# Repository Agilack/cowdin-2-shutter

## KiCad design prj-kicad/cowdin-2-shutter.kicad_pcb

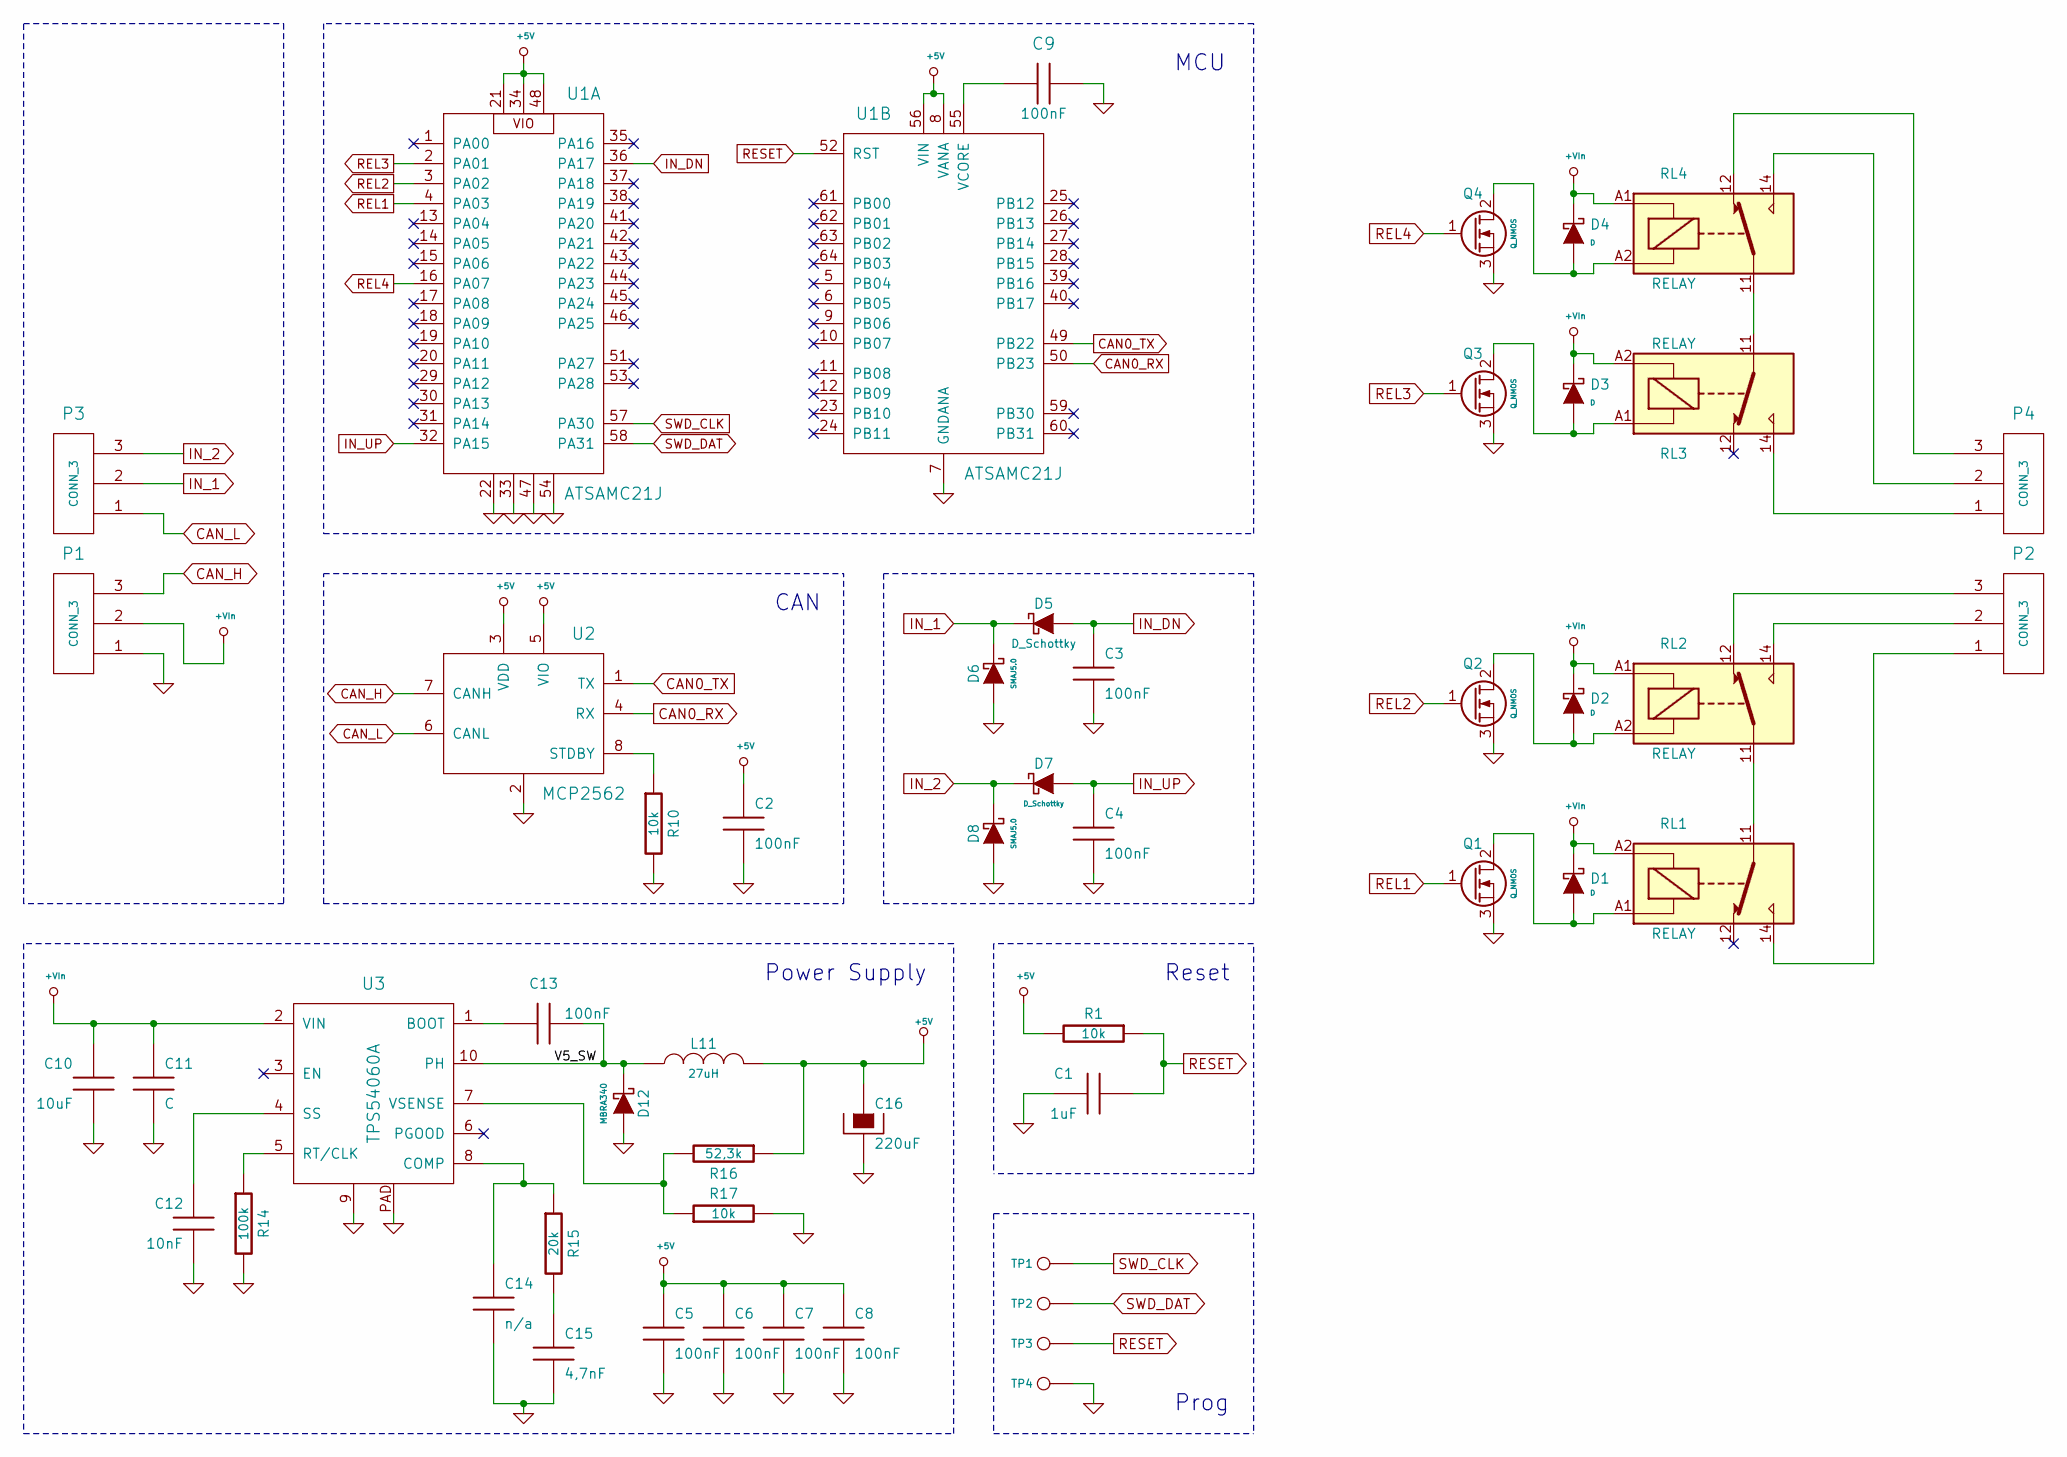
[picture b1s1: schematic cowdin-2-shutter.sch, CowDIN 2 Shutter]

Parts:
C1: 1uF; SMD0603
C2, C3, C4, C5, C6, C7, C8, C9, C13: 100nF; SMD0603
C10: 10uF; SMD1210
C11: C; SMD1210
C12: 10nF; SMD0603
C14: n/a; SMD0603
C15: 4,7nF; SMD0603
C16: 220uF; C_TPB_D4
D1, D2, D3, D4: D; SOD-123
D5, D7: D_Schottky; SOD-123
D6, D8: SMAJ5.0; DO214AC
D12: MBRA340; DO214AC
L11: 27uH; I_MSS1048
P1, P2, P3, P4: CONN_3; CONN_MC000035
Q1, Q2, Q3, Q4: Q_NMOS; SOT23-3
R1, R10, R17: 10k; SMD0603
R14: 100k; SMD0603
R15: 20k; SMD0603
R16: 52,3k; SMD0603
RL1, RL2, RL3, RL4: RELAY; RL_3451
TP1, TP2, TP3, TP4: CONN_1; TP_SMD
U1: ATSAMC21J; TQFP64
U2: MCP2562; SOIC-8E
U3: TPS54060A; MSOP10p

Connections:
5V: C2.1, C5.1, C6.1, C7.1, C8.1, C16.1, L11.2, R1.2, R16.1, U1.8 (VANA), U1.21, U1.34, U1.48, U1.56 (VIN), U2.3 (VDD), U2.5 (VIO)
/V5_SW: C13.2, D12.2 (K), L11.1, U3.10 (PH)
CAN0_RX: U1.50 (PB23), U2.4 (RX)
CAN0_TX: U1.49 (PB22), U2.1 (TX)
CAN_H: P1.3, U2.7 (CANH)
CAN_L: P3.1, U2.6 (CANL)
GND: C1.2, C2.2, C3.2, C4.2, C5.2, C6.2, C7.2, C8.2, C9.1, C10.2, C11.2, C12.2, C14.2, C15.2, C16.2, D6.1 (A), D8.1 (A), D12.1 (A), P1.1, Q1.3 (S), Q2.3 (S), Q3.3 (S), Q4.3 (S), R10.2, R14.2, R17.2, TP4.1, U1.7 (GNDANA), U1.22, U1.33, U1.47, U1.54, U2.2, U3.9, U3.PAD
IN_1: D5.2 (K), D6.2 (K), P3.2
IN_2: D7.2 (K), D8.2 (K), P3.3
IN_DN: C3.1, D5.1 (A), U1.36 (PA17)
IN_UP: C4.1, D7.1 (A), U1.32 (PA15)
unnamed: C9.2, U1.55 (VCORE)
unnamed: C12.1, U3.4 (SS)
unnamed: C13.1, U3.1 (BOOT)
unnamed: C14.1, R15.1, U3.8 (COMP)
unnamed: C15.1, R15.2
unnamed: D1.1 (A), Q1.2 (D), RL1.A1
unnamed: D2.1 (A), Q2.2 (D), RL2.A2
unnamed: D3.1 (A), Q3.2 (D), RL3.A1
unnamed: D4.1 (A), Q4.2 (D), RL4.A2
unnamed: P2.1, RL1.14
unnamed: P2.2, RL2.14
unnamed: P2.3, RL2.12
unnamed: P4.1, RL3.14
unnamed: P4.2, RL4.14
unnamed: P4.3, RL4.12
unnamed: R10.1, U2.8 (STDBY)
unnamed: R14.1, U3.5 (RT/CLK)
unnamed: R16.2, R17.1, U3.7 (VSENSE)
unnamed: RL1.11, RL2.11
unnamed: RL3.11, RL4.11
REL1: Q1.1 (G), U1.4 (PA03)
REL2: Q2.1 (G), U1.3 (PA02)
REL3: Q3.1 (G), U1.2 (PA01)
REL4: Q4.1 (G), U1.16 (PA07)
RESET: C1.1, R1.1, TP3.1, U1.52 (RST)
SWD_CLK: TP1.1, U1.57 (PA30)
SWD_DAT: TP2.1, U1.58 (PA31)
VIn: C10.1, C11.1, D1.2 (K), D2.2 (K), D3.2 (K), D4.2 (K), P1.2, RL1.A2, RL2.A1, RL3.A2, RL4.A1, U3.2 (VIN)

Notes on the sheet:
Power Supply
Reset
CAN
Prog
MCU

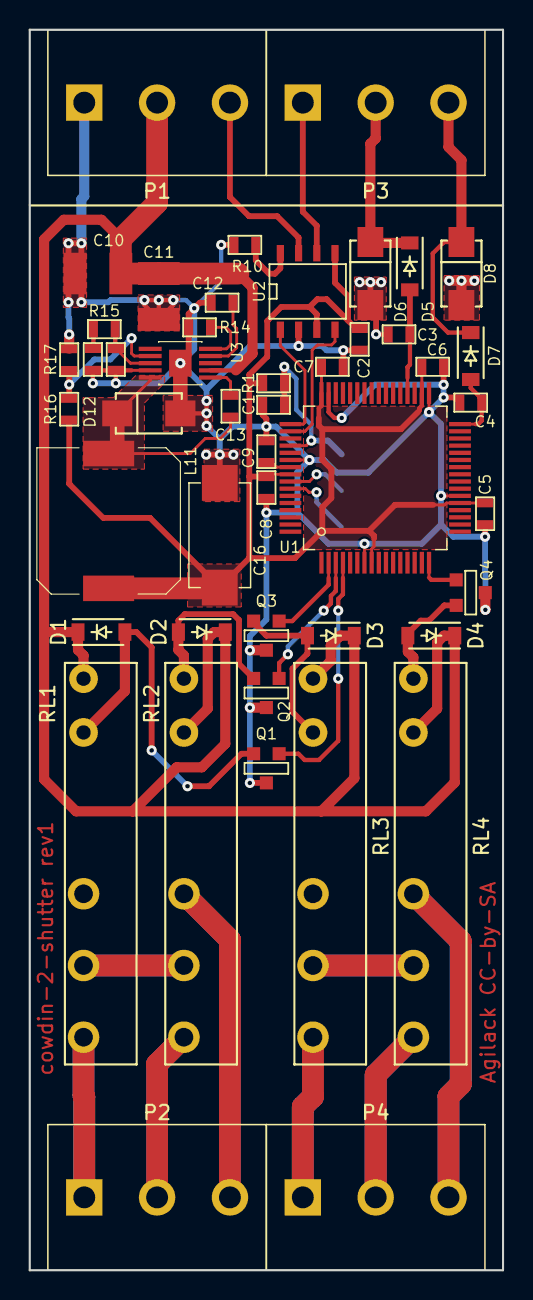
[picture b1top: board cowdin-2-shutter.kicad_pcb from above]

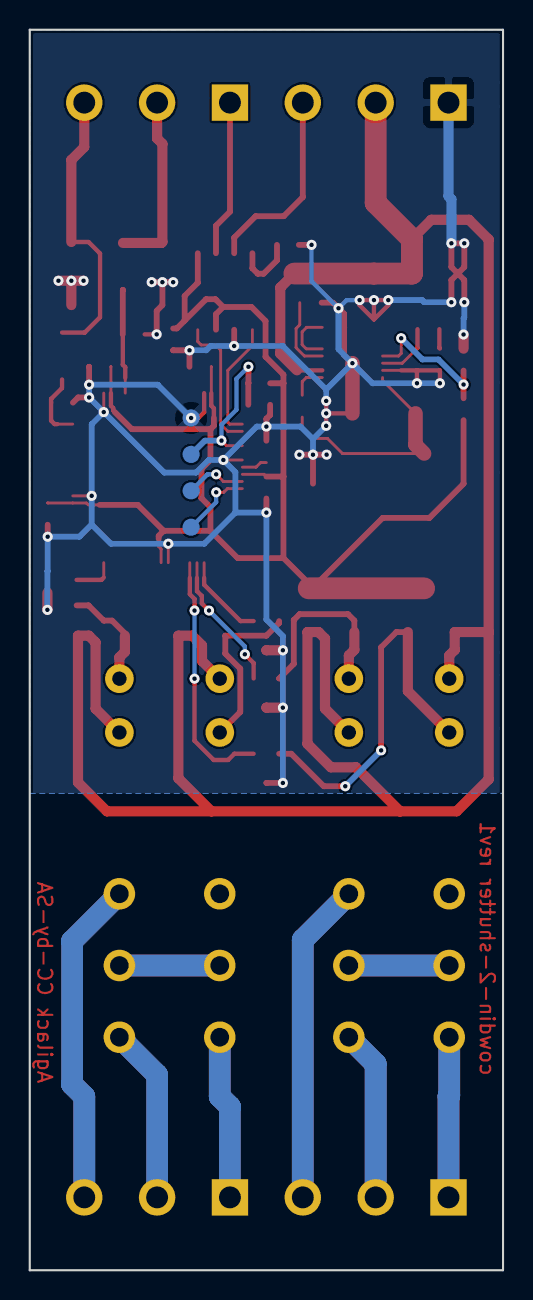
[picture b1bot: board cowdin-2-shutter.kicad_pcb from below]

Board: 2 copper layers, 33.0 x 86.5 mm, 51 parts (4 on the bottom side), 39 nets.

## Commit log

2020-05-19 = ADD: Create project, add relay and connectors into schematics, create board squeleton
2020-05-20 = ADD: Insert power supply for wide VIN (5-40V) to 5V internal
2020-05-21 = ADD: Insert processor and CAN interface (sch & routing)
2020-05-22 = ADD: Insert input and output interfaces
2020-05-26 = ADD: Create production files
2020-05-30 = ADD: Create basic firmware to test module
2020-06-13 Firmware: Refactor and clenaup, insert FSM, create modules for ios

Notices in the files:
prj-kicad/cowdin-2-shutter.kicad_pcb:
Agilack CC-by-SA
prj-kicad/cowdin-2-shutter.sch:
CC-by-SA
